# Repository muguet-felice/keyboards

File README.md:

# Muguet Keyboards

Firmware, source files, and documentation for Muguet keyboard projects.

## Repository structure

Each product is stored in its own folder.

Typical contents are:

- `firmware/`  
  Prebuilt firmware files.

- `source/`  
  QMK / Vial source files.

- `README.md`  
  Product-specific information.

- Setup guide PDF  
  Assembly and setup guide.

## Notes

Firmware files are intended for the products and configurations described in each product folder.

Unsupported microcontrollers, modified hardware, custom builds, and modified firmware are not officially supported.

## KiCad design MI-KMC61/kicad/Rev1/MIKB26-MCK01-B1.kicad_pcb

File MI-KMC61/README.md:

# MI-KMC61

MI-KMC61 is a 6-key macro keyboard by Muguet.

## Files

- `MI-KMC61_SetupGuide.pdf`  
  Setup guide and assembly manual.

- `QuickStart.pdf`  
  Package insert note / quick start notice.

- `firmware/`  
  Prebuilt firmware files.

- `source/`  
  QMK / Vial source files.

## Firmware

Use the latest `.hex` file in the `firmware` folder.

## Notes

This product is a DIY keyboard kit.  
Please read the setup guide before assembly, use, or firmware update.

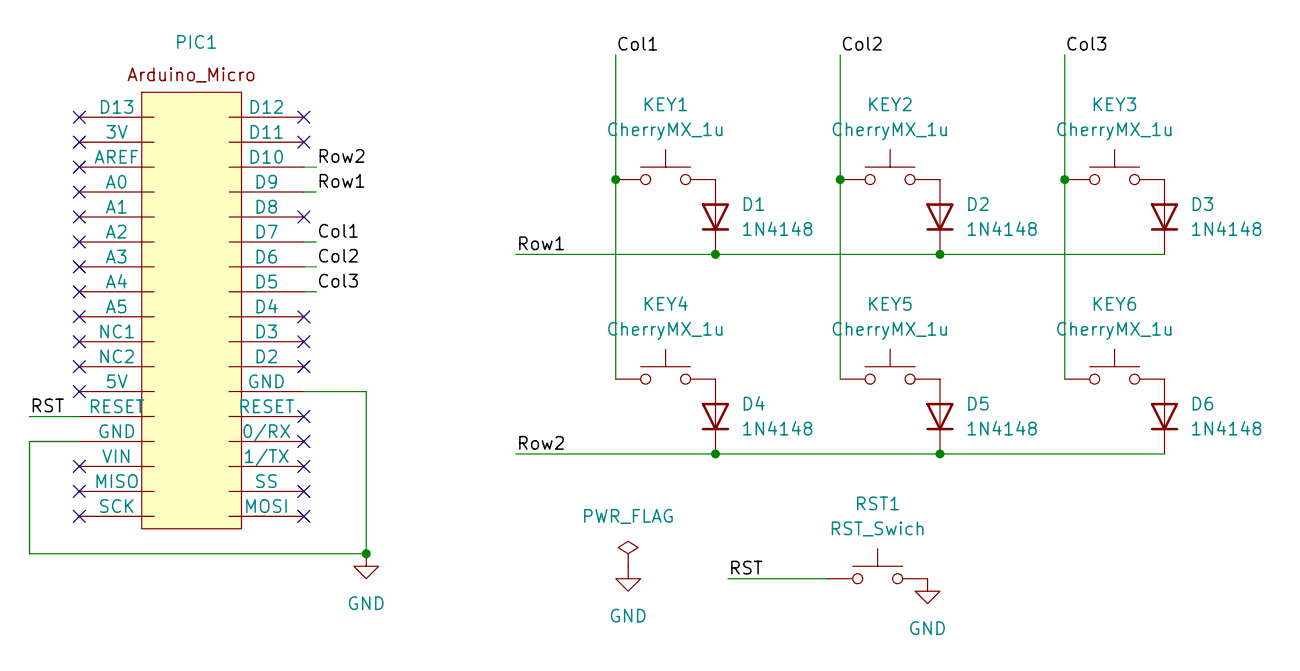
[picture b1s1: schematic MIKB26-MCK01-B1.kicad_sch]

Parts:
D1, D2, D3, D4, D5, D6: 1N4148; D_DO-35_SOD27_P7.62mm_Horizontal
KEY1, KEY2, KEY3, KEY4, KEY5, KEY6: CherryMX_1u; CherryMX_Solder_1u
PIC1: Arduino_Micro
RST1: RST_Swich; SW_PUSH_6mm

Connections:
/Col1: KEY1.2, KEY4.2, PIC1.D7
/Col2: KEY2.2, KEY5.2, PIC1.D6
/Col3: KEY3.2, KEY6.2, PIC1.D5
/RST: PIC1.RESET, RST1.1
/Row1: D1.1 (K), D2.1 (K), D3.1 (K), PIC1.D9
/Row2: D4.1 (K), D5.1 (K), D6.1 (K), PIC1.D10
GND: PIC1.GND, RST1.2
unnamed: D1.2 (A), KEY1.1
unnamed: D2.2 (A), KEY2.1
unnamed: D3.2 (A), KEY3.1
unnamed: D4.2 (A), KEY4.1
unnamed: D5.2 (A), KEY5.1
unnamed: D6.2 (A), KEY6.1

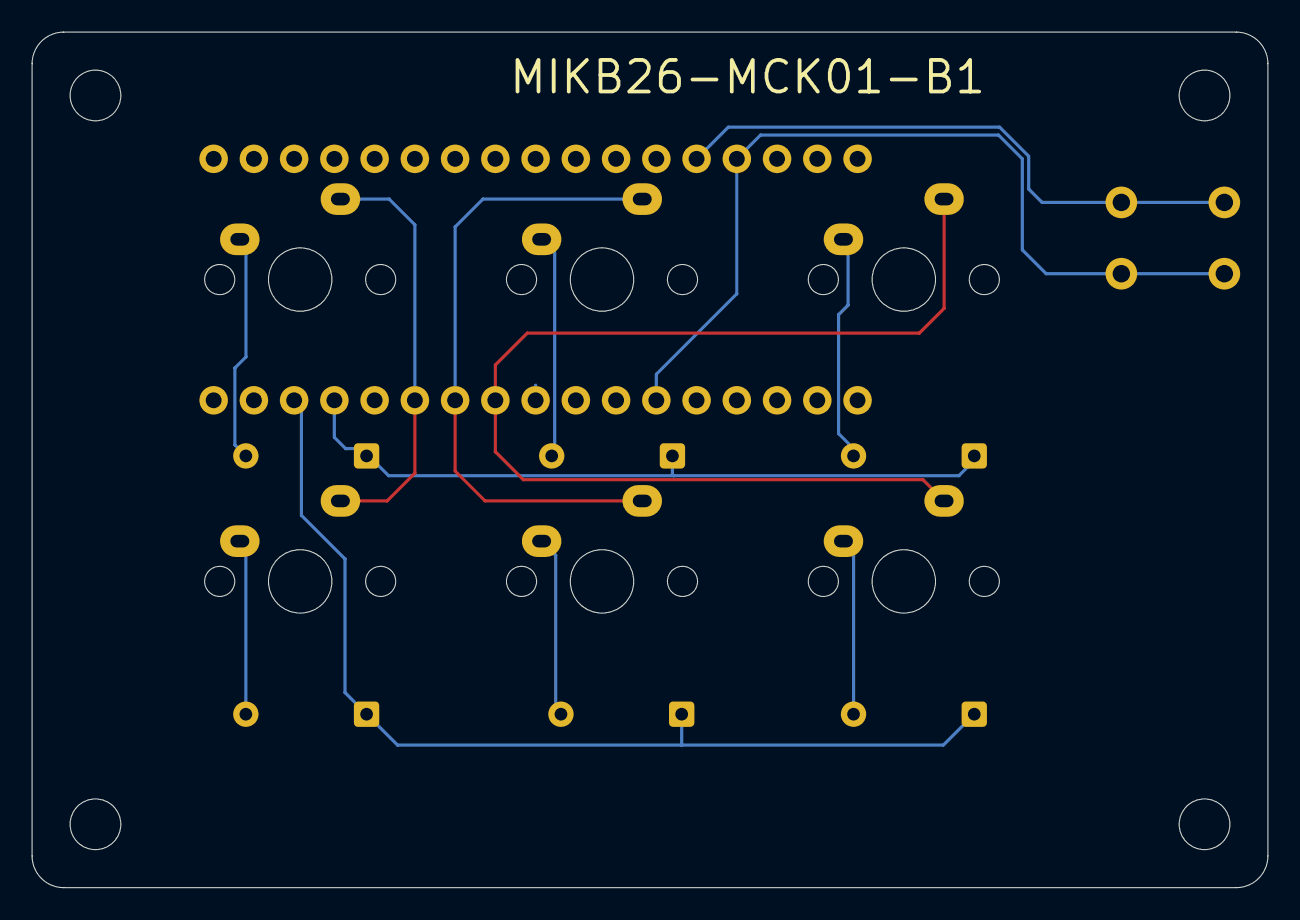
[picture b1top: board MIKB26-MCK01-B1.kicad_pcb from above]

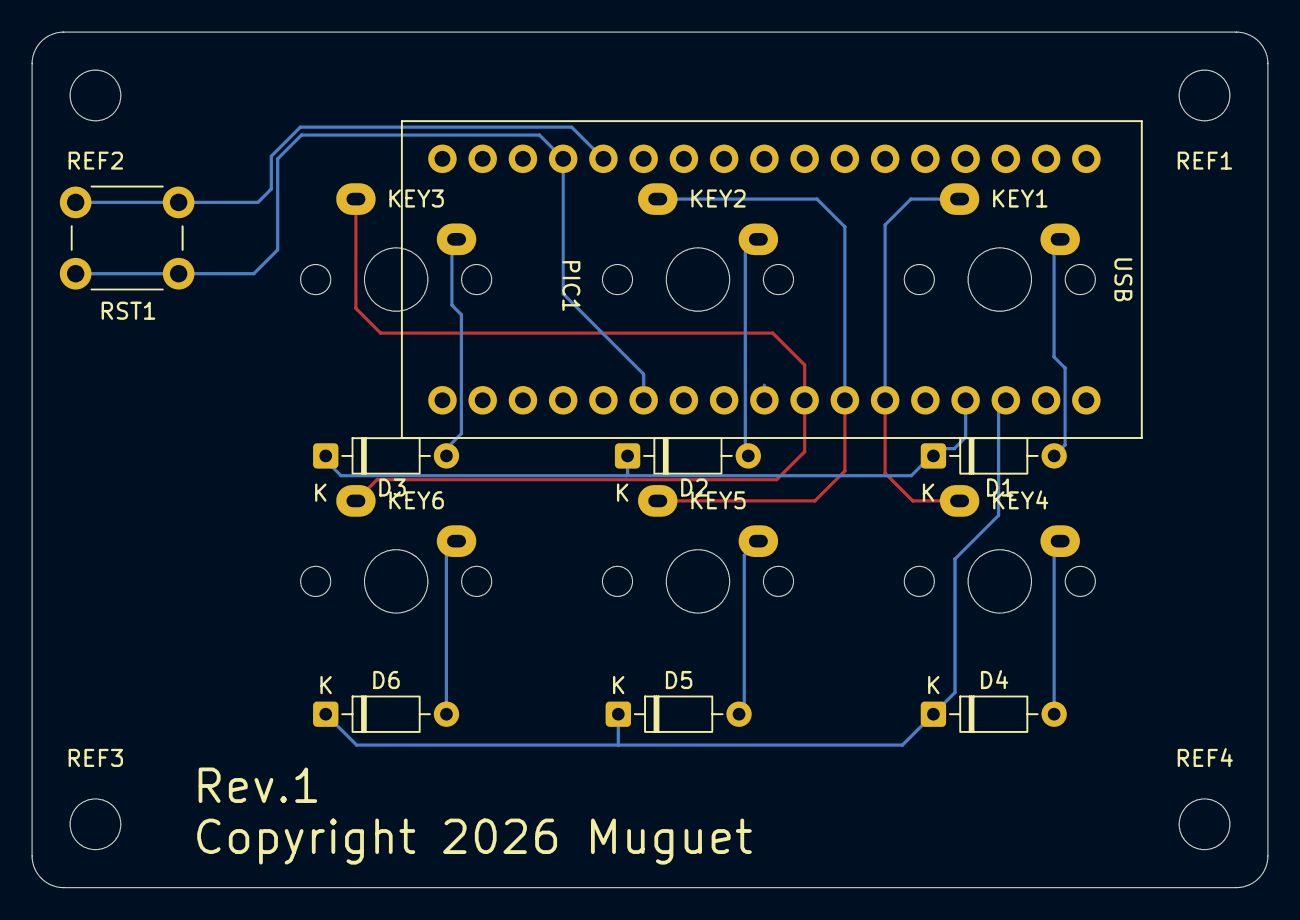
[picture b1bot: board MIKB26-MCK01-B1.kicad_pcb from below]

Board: 2 copper layers, 78.0 x 54.0 mm, 18 parts (8 on the bottom side), 13 nets.

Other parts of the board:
REF1, REF2, REF3, REF4: MountingHole_3.2mm_M3

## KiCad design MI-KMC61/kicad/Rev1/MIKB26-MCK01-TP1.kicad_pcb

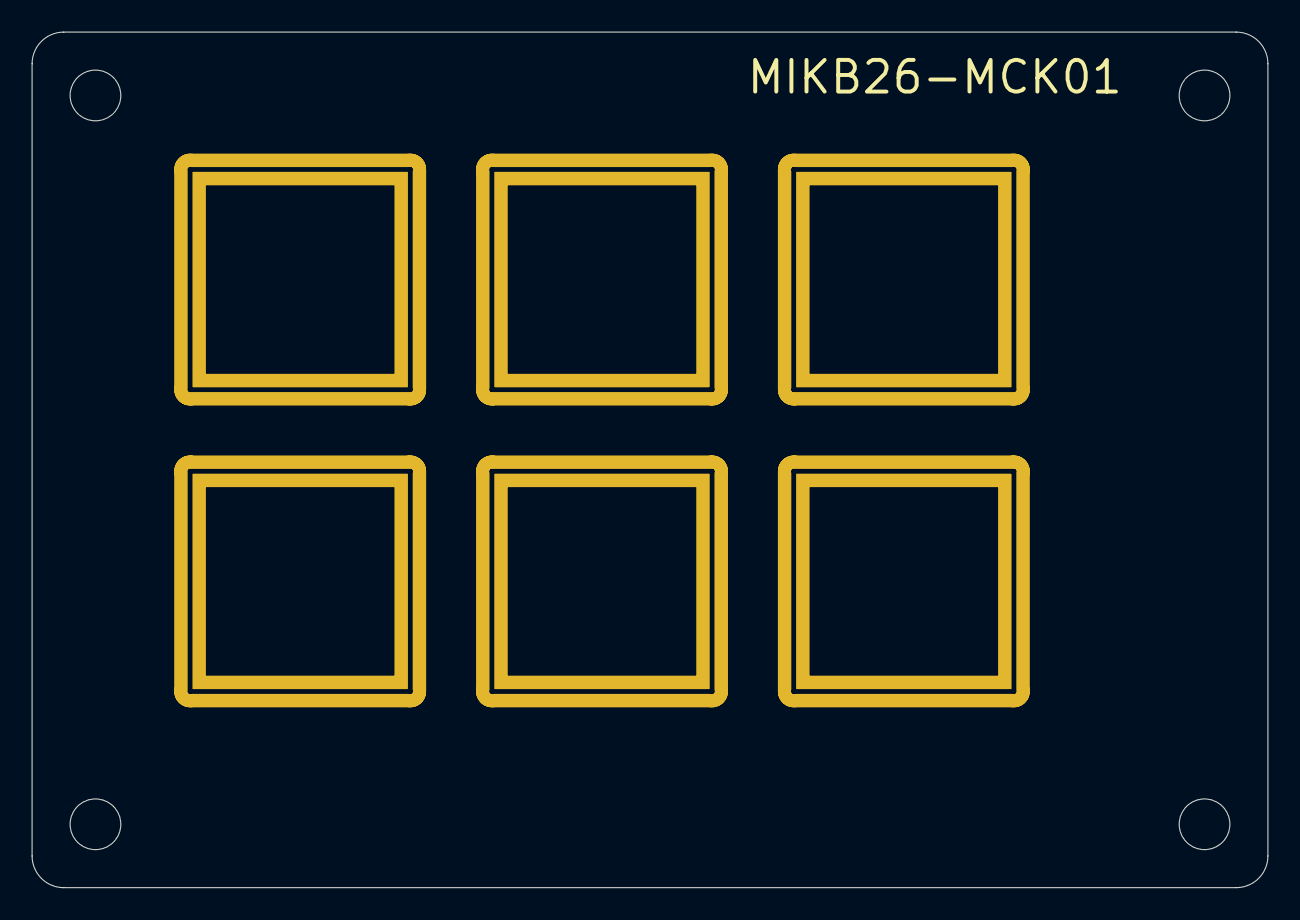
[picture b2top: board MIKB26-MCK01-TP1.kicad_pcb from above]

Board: 2 copper layers, 78.0 x 54.0 mm, 10 parts (0 on the bottom side), 3 nets, no tracks yet.

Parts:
KEY1, KEY2, KEY3, KEY4, KEY5, KEY6: CherryMX_1u; SW_Hole_TH_1u
REF1, REF2, REF3, REF4: MountingHole_3.2mm_M3

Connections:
/Col1: KEY1.1 (2_2), KEY4.1 (2_2)
/Col2: KEY2.1 (2_2), KEY5.1 (2_2)
/Col3: KEY3.1 (2_2), KEY6.1 (2_2)

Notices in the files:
MI-KMC61/kicad/Rev1/MIKB26-MCK01-B1.kicad_pcb:
Copyright 2026 Muguet
